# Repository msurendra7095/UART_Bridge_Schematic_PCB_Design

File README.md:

# UART Bridge - Schematic & PCB Design

## 📌 Overview
This project is a UART Bridge designed using KiCad. It enables communication between two UART devices by acting as an interface module.

## ⚙️ Features
- UART to UART communication bridge  
- Designed for reliable serial data transfer  
- Compact and optimized PCB layout  
- Suitable for embedded system debugging and communication  

## 🛠️ Tools & Technologies
- KiCad (Schematic & PCB Design)  
- UART Communication Protocol  

## 🔌 Applications
- Microcontroller communication (STM32 ↔ ESP32)  
- Debugging serial interfaces  
- Embedded system development  

## 👨‍💻 Author
Surendra

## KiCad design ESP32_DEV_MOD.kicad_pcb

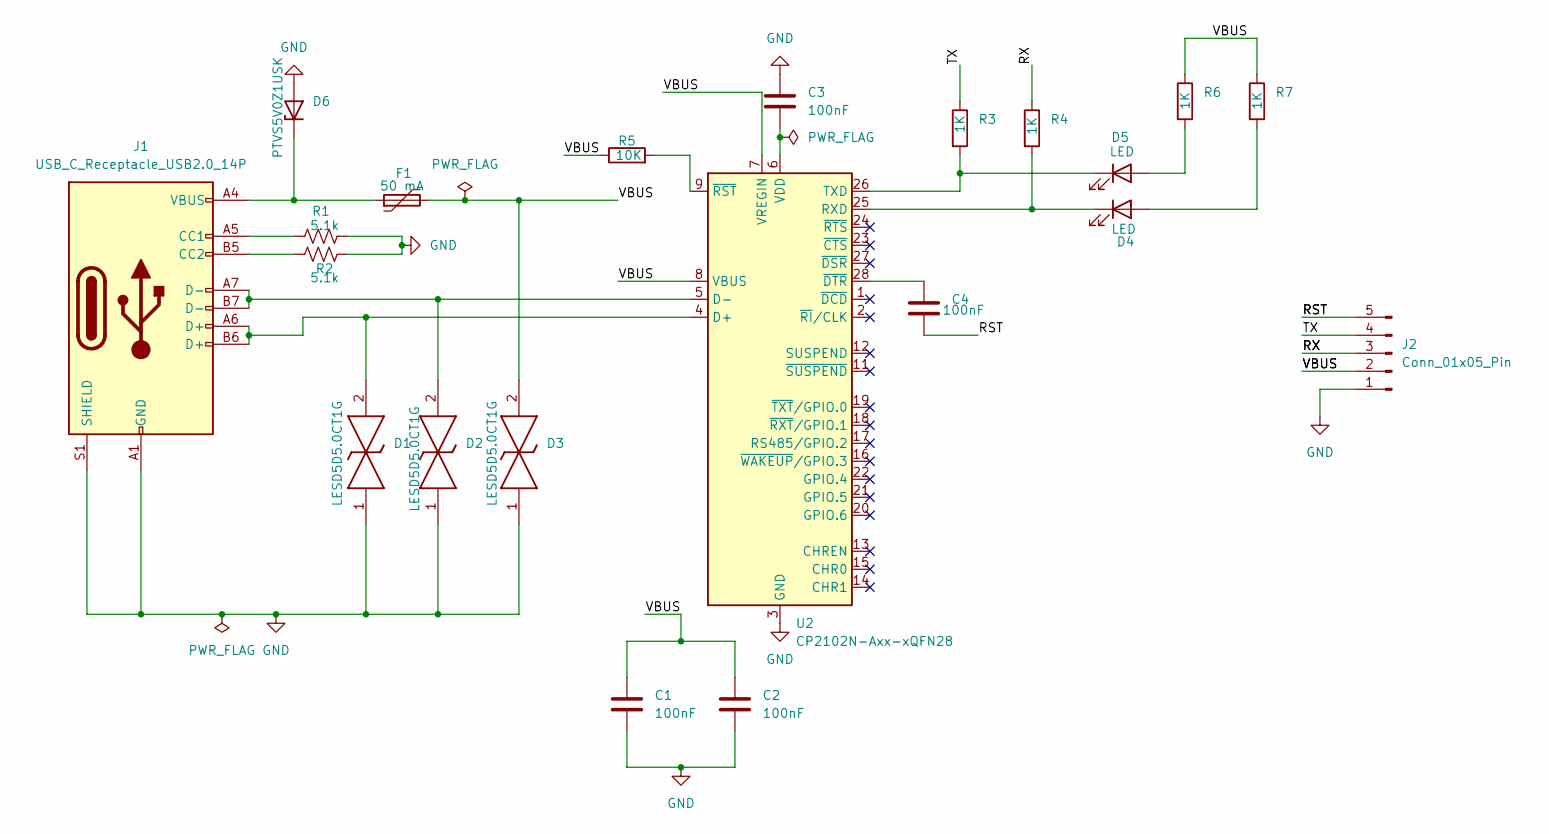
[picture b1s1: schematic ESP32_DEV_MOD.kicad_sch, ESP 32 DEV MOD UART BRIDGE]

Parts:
C1, C2, C3, C4: 100nF; C_0201_0603Metric
D1, D2, D3: LESD5D5.0CT1G; LESD5D50CT1G; Manufacturer_Part_Number LESD5D5.0CT1G
D4, D5: LED; LED_0201_0603Metric
D6: PTVS5V0Z1USK; Nexperia_DSN1608-2_1.6x0.8mm
F1: 50 mA; Fuse_1206_3216Metric
J1: USB_C_Receptacle_USB2.0_14P; USB_C_Receptacle_HRO_TYPE-C-31-M-12
J2: Conn_01x05_Pin; PinHeader_1x05_P2.54mm_Horizontal
R1, R2: 5.1k; R_0201_0603Metric
R3, R4, R6, R7: 1K; R_0201_0603Metric
R5: 10K; R_0201_0603Metric
U2: CP2102N-Axx-xQFN28; QFN-28-1EP_5x5mm_P0.5mm_EP3.35x3.35mm

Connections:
/RST: C4.2, J2.5
/RX: J2.3, R4.1
/TX: J2.4, R3.1
/VBUS: C1.1, C2.1, D3.2, F1.2, J2.2, R5.1, R6.1, R7.1, U2.7 (VREGIN), U2.8 (VBUS)
GND: C1.2, C2.2, C3.1, D1.1, D2.1, D3.1, D6.2 (A), J1.A1 (GND), J1.A12 (GND), J1.B1 (GND), J1.B12 (GND), J1.S1 (SHIELD), J2.1, R1.2, R2.2, U2.3 (GND), U2.29 (GND)
unnamed: D4.2 (A), R7.2
unnamed: D4.1 (K), R4.2, U2.25 (RXD)
unnamed: D5.2 (A), R6.2
unnamed: D5.1 (K), R3.2, U2.26 (TXD)
unnamed: D6.1 (K), F1.1, J1.A4 (VBUS), J1.A9 (VBUS), J1.B4 (VBUS), J1.B9 (VBUS)
unnamed: J1.A5 (CC1), R1.1
unnamed: J1.B5 (CC2), R2.1
unnamed: D1.2, J1.A6 (D+), J1.B6 (D+), U2.4 (D+)
unnamed: D2.2, J1.A7 (D-), J1.B7 (D-), U2.5 (D-)
unnamed: C3.2, U2.6 (VDD)
unnamed: C4.1, U2.28 (~DTR)
unnamed: R5.2, U2.9 (~RST)

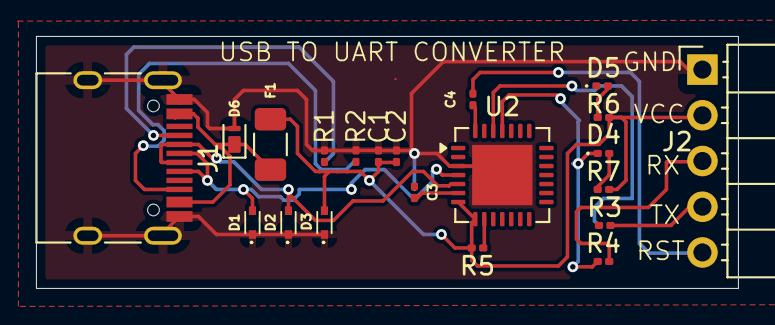
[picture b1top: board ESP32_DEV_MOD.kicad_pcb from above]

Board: 2 copper layers, 39.0 x 14.0 mm, 21 parts (0 on the bottom side), 17 nets.

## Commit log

2026-03-28 UART Bridge PCB Design using KiCad
